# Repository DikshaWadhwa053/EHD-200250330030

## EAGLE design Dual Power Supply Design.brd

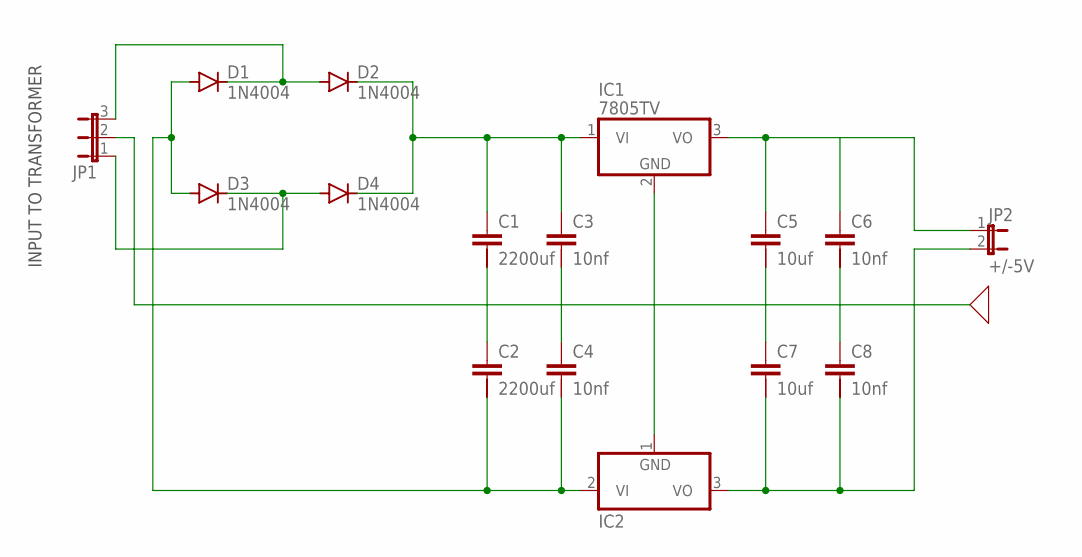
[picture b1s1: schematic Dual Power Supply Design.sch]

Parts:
C1, C2: 2200uf; C2.5/5-2
C3, C4, C6, C8: 10nf; C2.5/5-2
C5, C7: 10uf; C2.5/5-2
D1, D2, D3, D4: 1N4004; DO41-10
IC1: 7805TV; TO220V
IC2: 7905T; TO220H
JP1: JP2W
JP2: +/-5V; JP1

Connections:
unnamed: D1.C, D2.A, JP1.3
unnamed: C1.1, C3.1, D2.C, D4.C, IC1.1 (VI)
unnamed: D3.C, D4.A, JP1.1
unnamed: C2.2, C4.2, D1.A, D3.A, IC2.2 (VI)
unnamed: C1.2, C2.1
unnamed: C3.2, C4.1
unnamed: C5.1, IC1.3 (VO), JP2.1
unnamed: IC1.2 (GND), IC2.1 (GND)
unnamed: C5.2, C7.1
unnamed: C7.2, C8.2, IC2.3 (VO), JP2.2
unnamed: C6.2, C8.1

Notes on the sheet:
INPUT TO TRANSFORMER

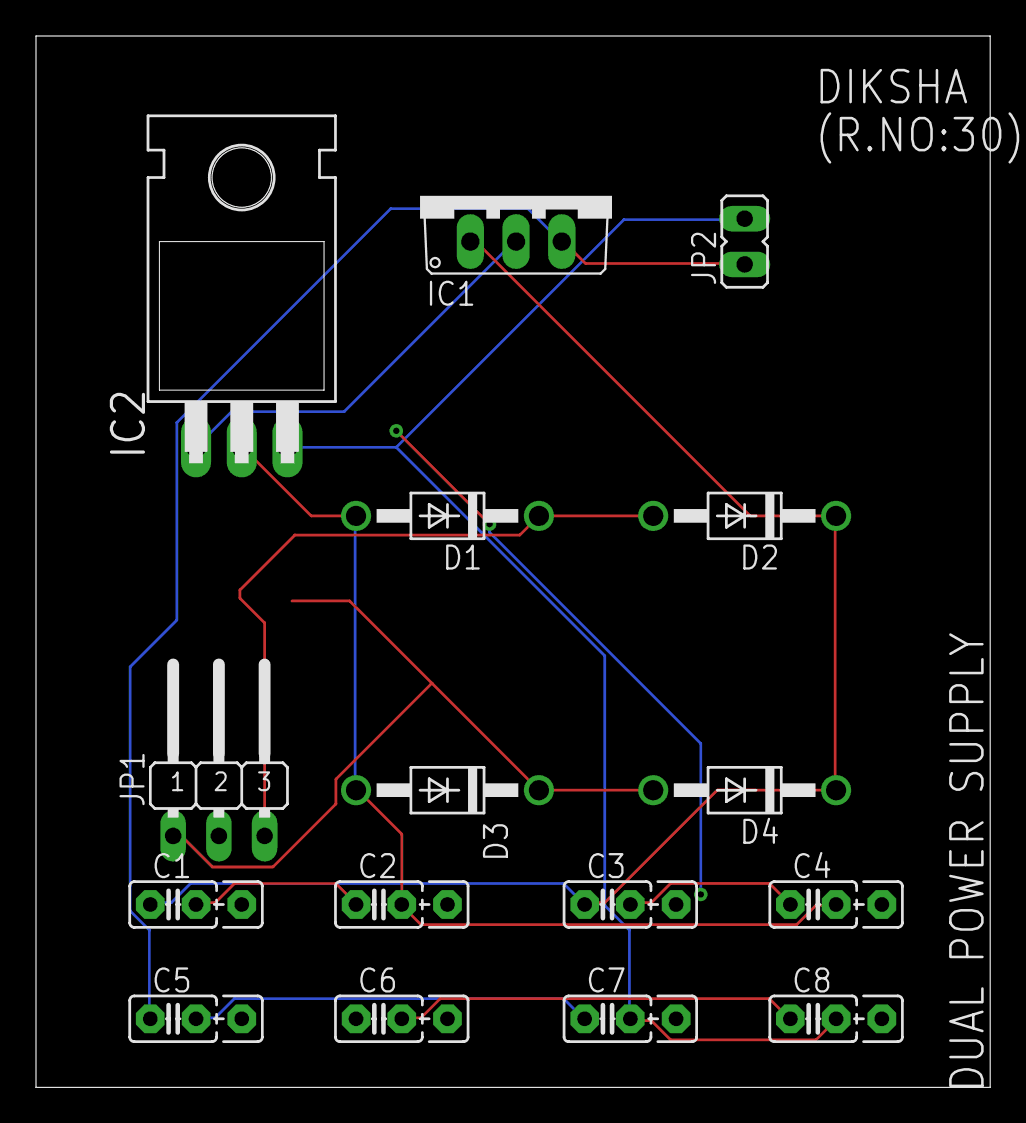
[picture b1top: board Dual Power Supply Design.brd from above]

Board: 2 copper layers, 53.0 x 58.4 mm, 16 parts (0 on the bottom side), 11 nets.

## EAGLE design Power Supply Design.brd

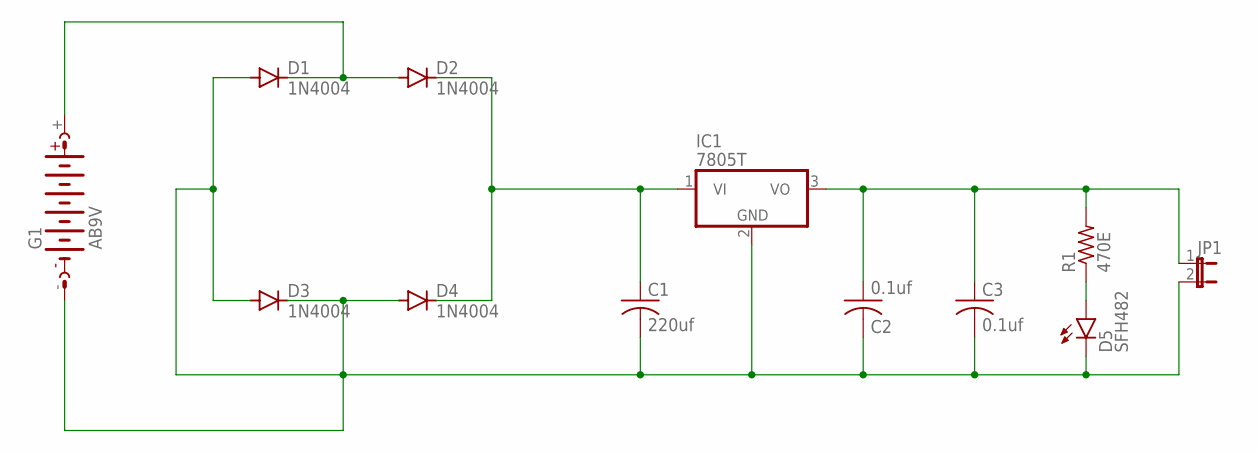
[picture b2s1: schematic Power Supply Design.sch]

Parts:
C1: 220uf; C050-030X075
C2, C3: 0.1uf; C050-030X075
D1, D2, D3, D4: 1N4004; DO41-10
D5: SFH482
G1: AB9V
IC1: 7805T; TO220H
JP1: JP1E; JP1
R1: 470E; 0204/7

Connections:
unnamed: D1.C, D2.A, G1.+
unnamed: C1.1, D2.C, D4.C, IC1.1 (VI)
unnamed: C2.1, C3.1, IC1.3 (VO), JP1.1, R1.2
unnamed: D5.A, R1.1
unnamed: C1.2, C2.2, C3.2, D1.A, D3.A, D3.C, D4.A, D5.K (C), G1.-, IC1.2 (GND), JP1.2

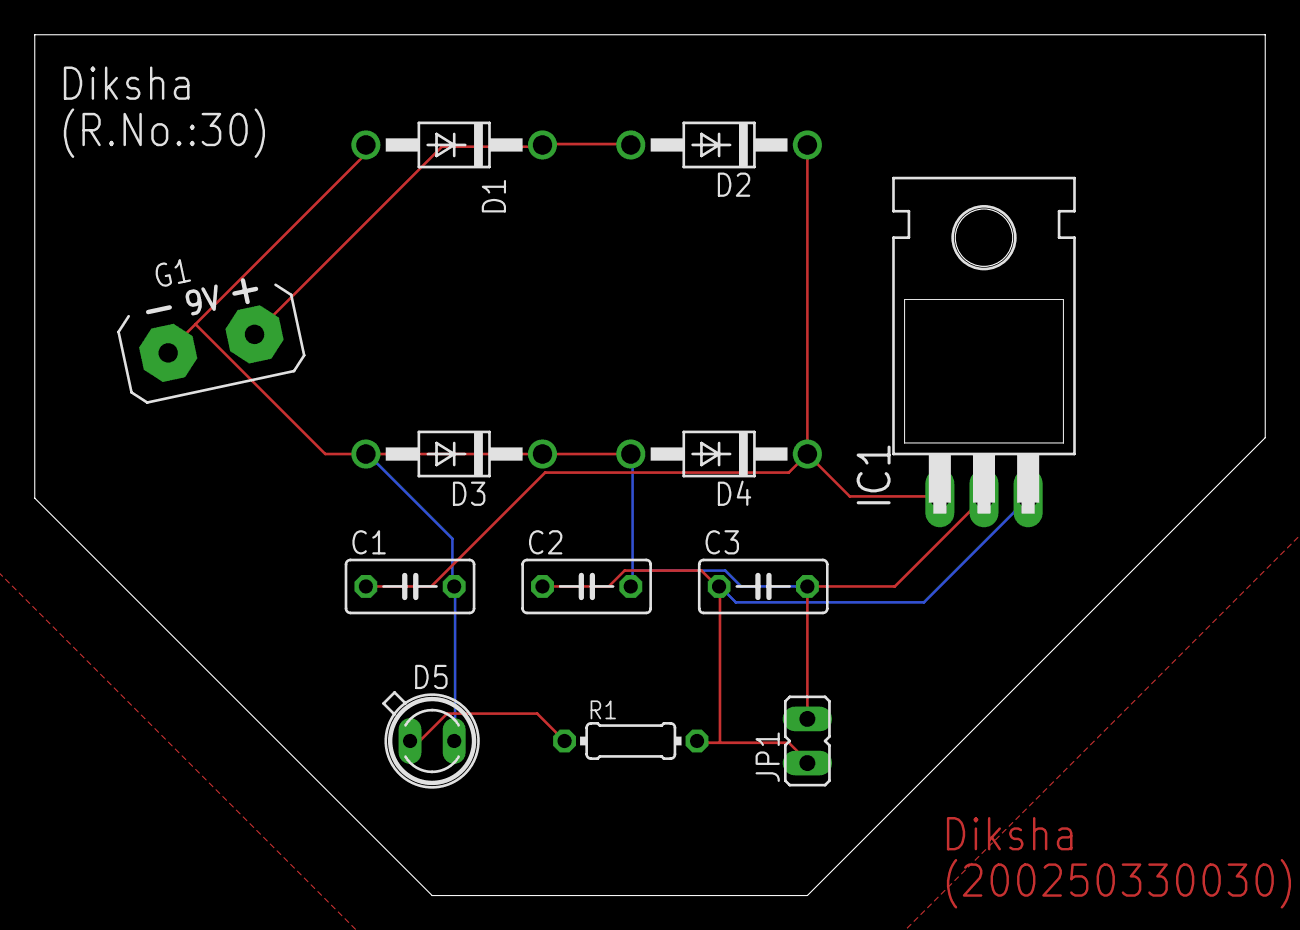
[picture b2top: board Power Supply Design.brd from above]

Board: 2 copper layers, 70.8 x 49.5 mm, 12 parts (0 on the bottom side), 5 nets.
